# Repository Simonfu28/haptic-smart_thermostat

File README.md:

# haptic-smart_thermostat
Smart home thermostat with BLDC haptic feedback

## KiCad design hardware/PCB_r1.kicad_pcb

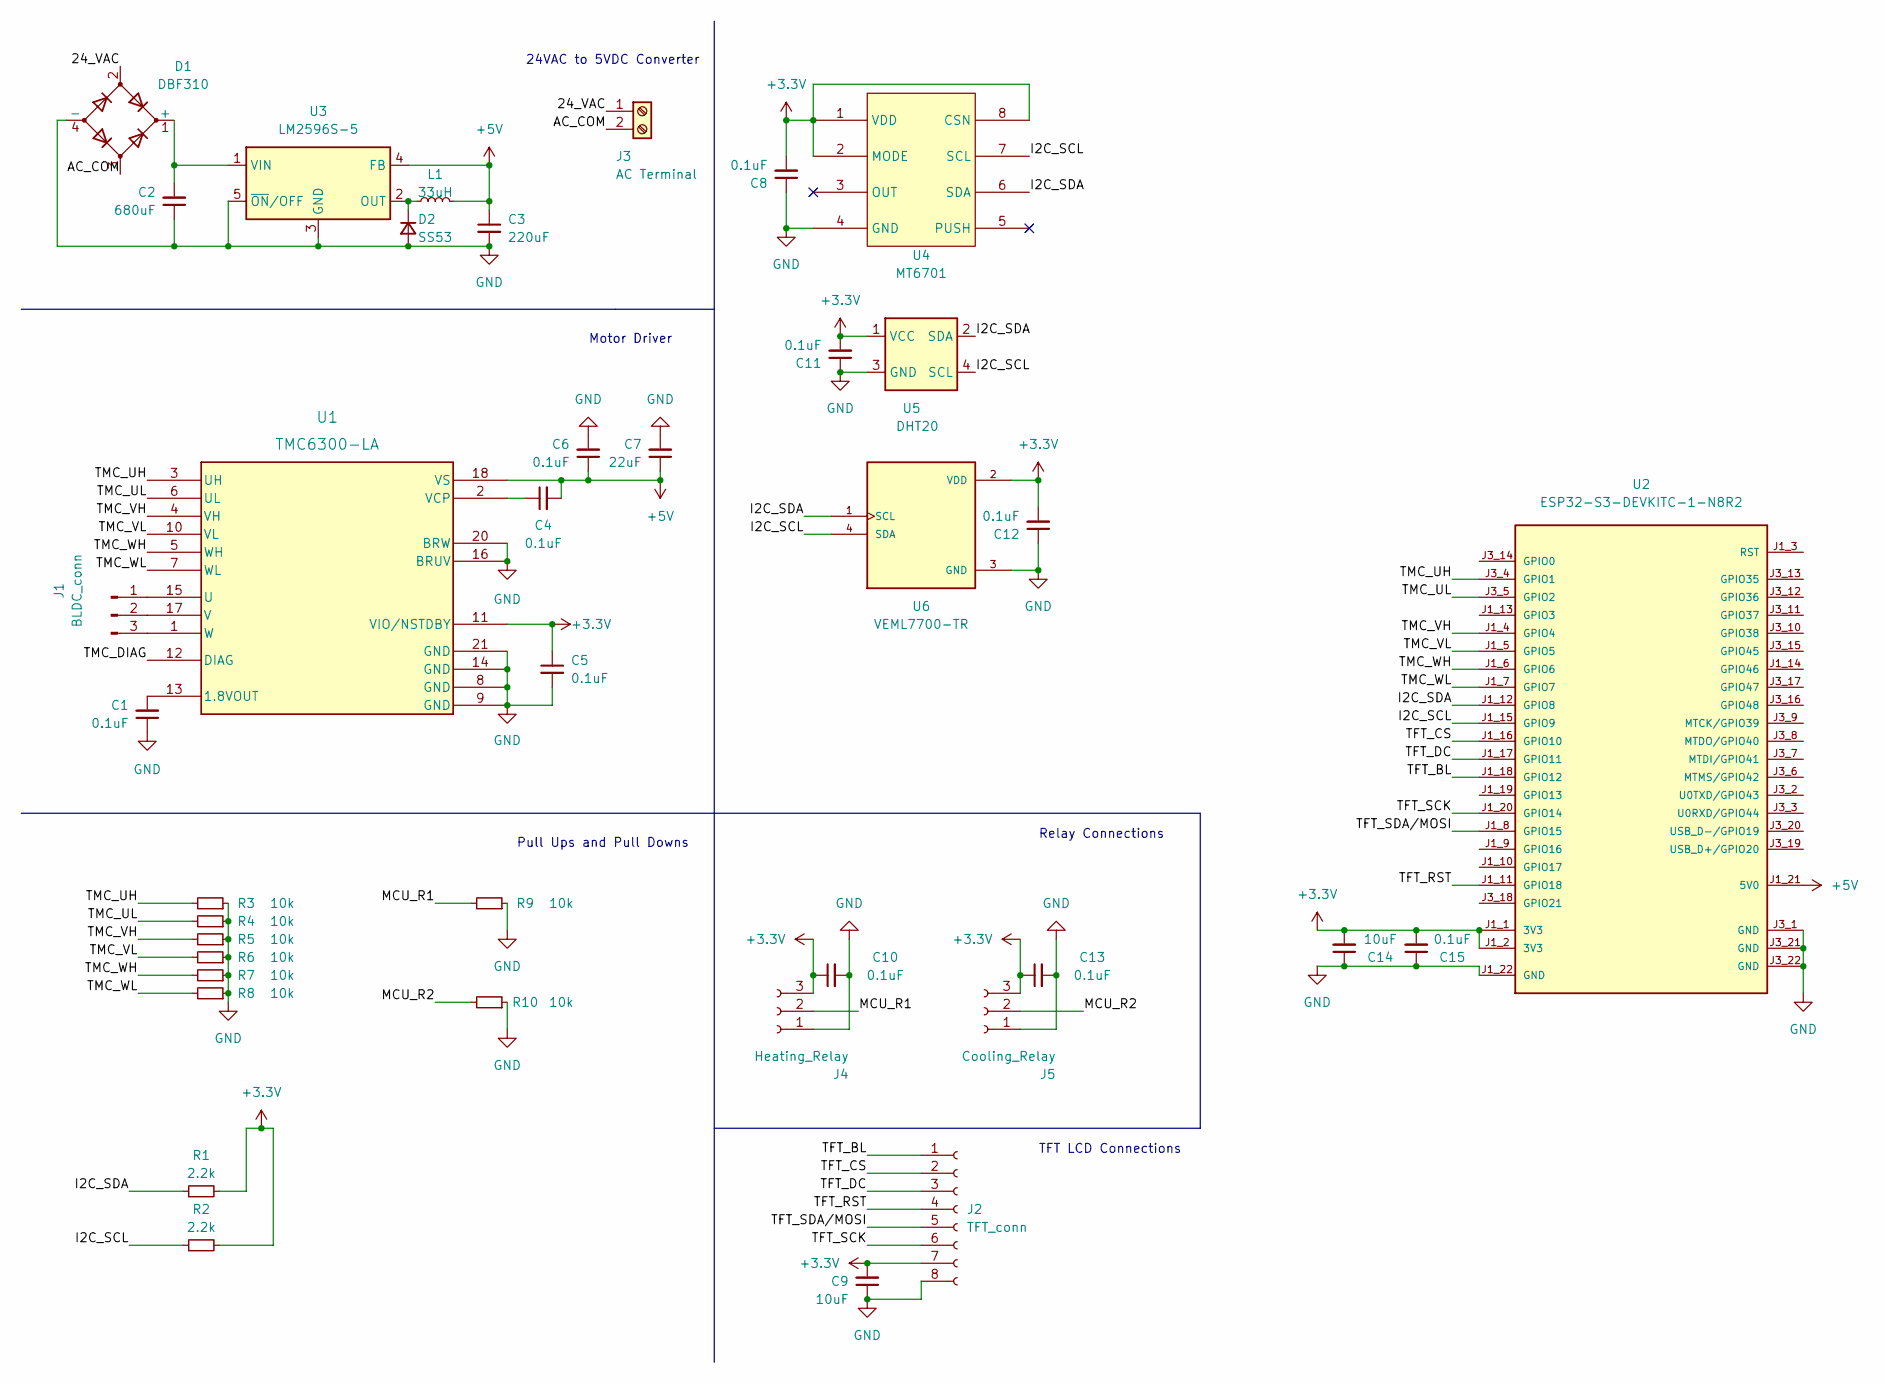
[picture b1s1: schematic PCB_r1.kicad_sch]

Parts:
C1, C4, C5, C6, C8, C10, C11, C12, C13, C15: 0.1uF; C_0603_1608Metric
C2: 680uF; CP_Elec_8x10
C3: 220uF; CP_Elec_8x10
C7: 22uF; C_0805_2012Metric
C9, C14: 10uF; C_0805_2012Metric
D1: DBF310; DBF_DIO-L
D2: SS53; D_SMB
J1: BLDC_conn; Molex_PicoBlade_53047-0310_1x03_P1.25mm_Vertical
J2: TFT_conn; Molex_Panelmate_53780-0870_1x08-1MP_P1.25mm_Horizontal
J3: AC Terminal; PinHeader_1x02_P2.54mm_Vertical
J4: Heating_Relay; PinHeader_1x03_P2.54mm_Vertical
J5: Cooling_Relay; PinHeader_1x03_P2.54mm_Vertical
L1: 33uH; L_12x12mm_H8mm
R1, R2: 2.2k; R_0603_1608Metric
R3, R4, R5, R6, R7, R8, R9, R10: 10k; R_0201_0603Metric
U1: TMC6300-LA; 21-100586_K2033&plus_1C_ADI-M
U2: ESP32-S3-DEVKITC-1-N8R2; XCVR_ESP32-S3-DEVKITC-1-N8R2; PARTREV V1
U3: LM2596S-5; TO-263-5_TabPin3
U4: MT6701
U5: DHT20; Aosong_DHT11_5.5x12.0_P2.54mm
U6: VEML7700-TR; XDCR_VEML7700-TR; PARTREV 1.6

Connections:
+3.3V: C5.1, C8.2, C9.2, C10.1, C11.2, C12.2, C13.1, C14.2, C15.2, J2.7, J4.3, J5.3, R1.2, R2.2, U1.11 (VIO/NSTDBY), U2.J1_1 (3V3), U2.J1_2 (3V3), U4.1 (VDD), U4.2 (MODE), U4.8 (CSN), U5.1 (VCC), U6.2 (VDD)
+5V: C3.1, C4.2, C6.1, C7.1, L1.2, U1.18 (VS), U2.J1_21 (5V0), U3.4 (FB)
/24_VAC: D1.2, J3.1
/AC_COM: D1.3, J3.2
/I2C_SCL: R2.1, U2.J1_15 (GPIO9), U4.7 (SCL), U5.4 (SCL), U6.4 (SDA)
/I2C_SDA: R1.1, U2.J1_12 (GPIO8), U4.6 (SDA), U5.2 (SDA), U6.1 (SCL)
/MCU_R1: J4.2, R9.2
/MCU_R2: J5.2, R10.2
/TFT_BL: J2.1, U2.J1_18 (GPIO12)
/TFT_CS: J2.2, U2.J1_16 (GPIO10)
/TFT_DC: J2.3, U2.J1_17 (GPIO11)
/TFT_RST: J2.4, U2.J1_11 (GPIO18)
/TFT_SCK: J2.6, U2.J1_20 (GPIO14)
/TFT_SDA/MOSI: J2.5, U2.J1_8 (GPIO15)
/TMC_DIAG: U1.12 (DIAG)
/TMC_UH: R3.2, U1.3 (UH), U2.J3_4 (GPIO1)
/TMC_UL: R4.2, U1.6 (UL), U2.J3_5 (GPIO2)
/TMC_VH: R5.2, U1.4 (VH), U2.J1_4 (GPIO4)
/TMC_VL: R6.2, U1.10 (VL), U2.J1_5 (GPIO5)
/TMC_WH: R7.2, U1.5 (WH), U2.J1_6 (GPIO6)
/TMC_WL: R8.2, U1.7 (WL), U2.J1_7 (GPIO7)
GND: C1.1, C2.1, C3.2, C5.2, C6.2, C7.2, C8.1, C9.1, C10.2, C11.1, C12.1, C13.2, C14.1, C15.1, D1.4 (-), D2.2 (A), J2.8, J4.1, J5.1, R3.1, R4.1, R5.1, R6.1, R7.1, R8.1, R9.1, R10.1, U1.8 (GND), U1.9 (GND), U1.14 (GND), U1.16 (BRUV), U1.20 (BRW), U1.21 (GND), U2.J1_22 (GND), U2.J3_1 (GND), U2.J3_21 (GND), U2.J3_22 (GND), U3.3 (GND), U3.5 (~ON/OFF), U4.4 (GND), U5.3 (GND), U6.3 (GND)
unnamed: C1.2, U1.13 (1.8VOUT)
unnamed: C2.2, D1.1 (+), U3.1 (VIN)
unnamed: C4.1, U1.2 (VCP)
unnamed: D2.1 (K), L1.1, U3.2 (OUT)
unnamed: J1.1, U1.15 (U)
unnamed: J1.2, U1.17 (V)
unnamed: J1.3, U1.1 (W)

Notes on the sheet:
Motor Driver
TFT LCD Connections
Pull Ups and Pull Downs
24VAC to 5VDC Converter
Relay Connections

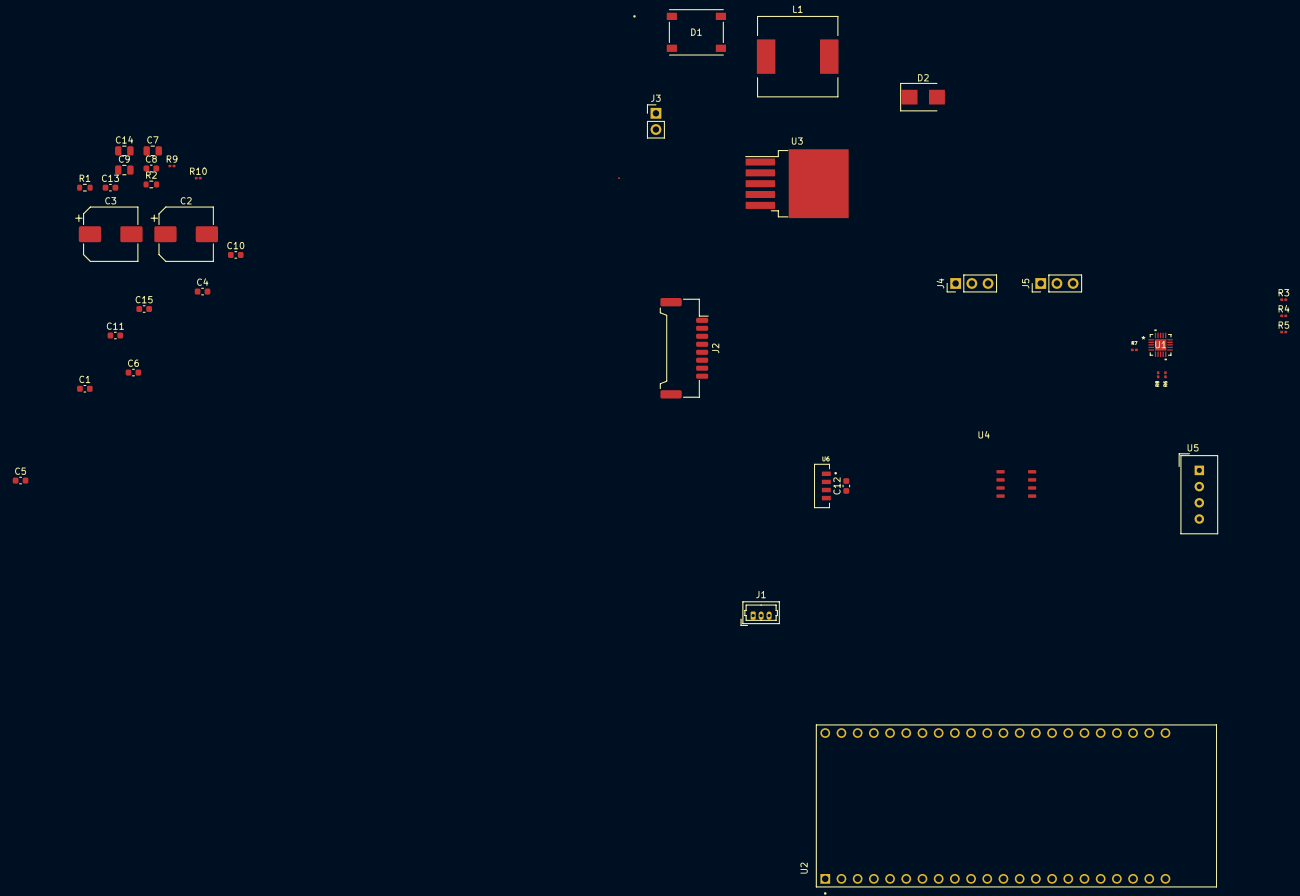
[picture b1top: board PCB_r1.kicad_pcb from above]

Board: 2 copper layers, 39 parts (0 on the bottom side), 28 nets.

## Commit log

2024-02-27 added pcb files to git
